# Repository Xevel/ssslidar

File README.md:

# ssslidar
Small Solid State Lidar

The SSSlidar is a (W) 29 x (L) 39 x (H) 21 mm sensor. It is composed of 13 TOF distance sensors, 12 arranged in circular pattern and 1 looking perpendicular to the others.

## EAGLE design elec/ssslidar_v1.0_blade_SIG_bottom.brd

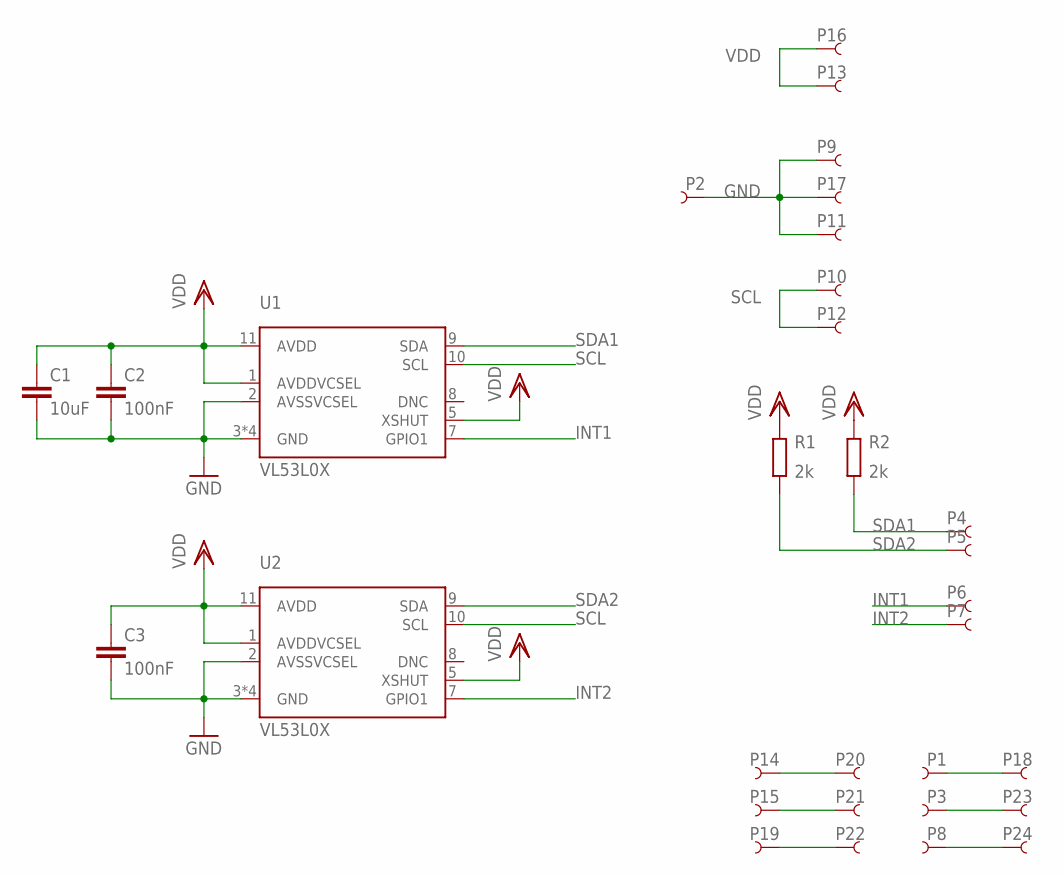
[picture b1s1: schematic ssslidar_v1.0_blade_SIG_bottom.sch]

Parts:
C1: 10uF; 0805_N
C2, C3: 100nF; 0402_N
P1, P3, P4, P5, P6, P7, P8, P14, P15, P18, P19, P20, P21, P22, P23, P24: PIN_SMD_0.8X1_RECT
P2, P9, P10, P11, P12, P13, P16, P17: PIN_SMD_1X2
R1, R2: 2k; 0402_N
U1, U2: VL53L0X

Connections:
GND: C1.2, C2.2, C3.2, P2.P$1, P9.P$1, P11.P$1, P17.P$1, U1.2 (AVSSVCSEL), U1.3 (GND), U1.4 (GND), U1.6 (GND), U1.12 (GND), U2.2 (AVSSVCSEL), U2.3 (GND), U2.4 (GND), U2.6 (GND), U2.12 (GND)
INT1: P6.PIN, U1.7 (GPIO1)
INT2: P7.PIN, U2.7 (GPIO1)
unnamed: P14.PIN, P20.PIN
unnamed: P15.PIN, P21.PIN
unnamed: P19.PIN, P22.PIN
unnamed: P1.PIN, P18.PIN
unnamed: P3.PIN, P23.PIN
unnamed: P8.PIN, P24.PIN
SCL: P10.P$1, P12.P$1, U1.10 (SCL), U2.10 (SCL)
SDA1: P4.PIN, R2.1, U1.9 (SDA)
SDA2: P5.PIN, R1.1, U2.9 (SDA)
VDD: C1.1, C2.1, C3.1, P13.P$1, P16.P$1, R1.2, R2.2, U1.1 (AVDDVCSEL), U1.5 (XSHUT), U1.11 (AVDD), U2.1 (AVDDVCSEL), U2.5 (XSHUT), U2.11 (AVDD)

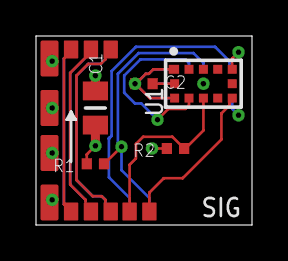
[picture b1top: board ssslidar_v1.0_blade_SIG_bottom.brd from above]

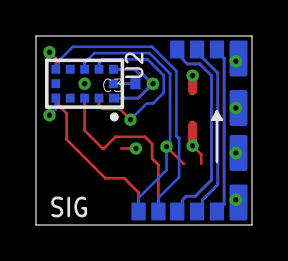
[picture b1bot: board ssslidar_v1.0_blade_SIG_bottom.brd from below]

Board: 4 copper layers, 12.0 x 10.5 mm, 31 parts (14 on the bottom side), 13 nets.

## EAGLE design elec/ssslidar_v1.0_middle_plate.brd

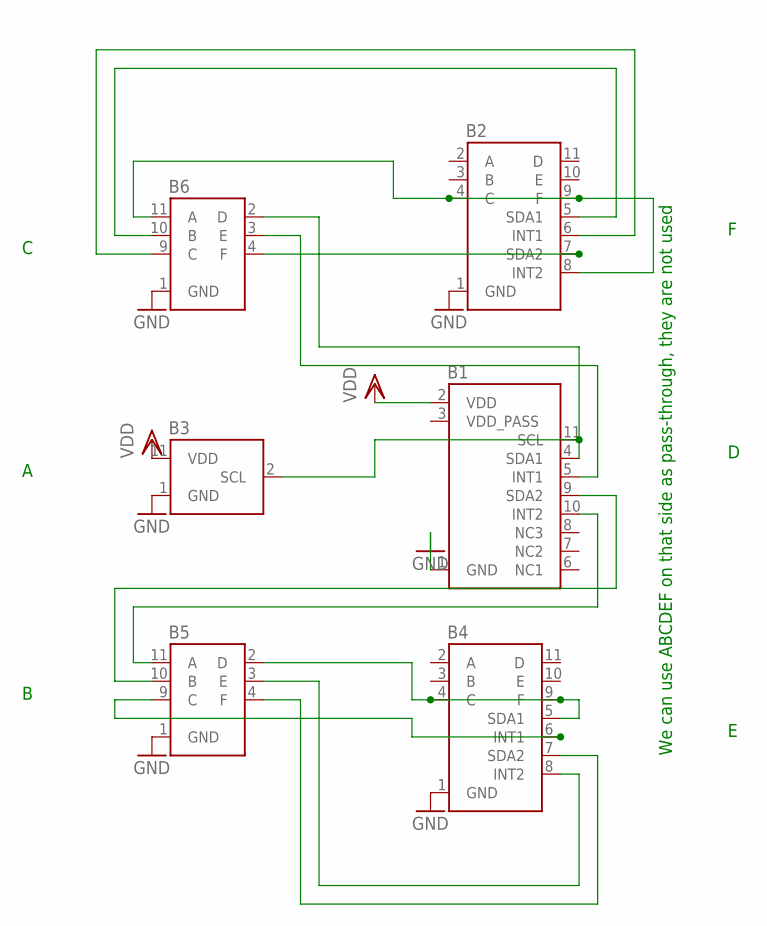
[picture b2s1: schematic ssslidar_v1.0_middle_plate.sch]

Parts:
B1: BLADE_PWR_BOTTOM; BLADE
B2, B4: BLADE_SIG_BOTTOM; BLADE
B3: BLADE_PWR_TOP; BLADE
B5, B6: BLADE_SIG_TOP; BLADE

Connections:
GND: B1.1 (GND), B2.1 (GND), B3.1 (GND), B4.1 (GND), B5.1 (GND), B6.1 (GND)
unnamed: B1.11 (SCL), B3.2 (SCL)
unnamed: B2.4 (C), B2.8 (INT2), B2.9 (F), B6.11 (A)
unnamed: B2.5 (SDA1), B6.10 (B)
unnamed: B2.6 (INT1), B6.9 (C)
unnamed: B1.5 (INT1), B6.3 (E)
unnamed: B2.7 (SDA2), B6.4 (F)
unnamed: B4.8 (INT2), B5.3 (E)
unnamed: B4.4 (C), B4.5 (SDA1), B4.9 (F), B5.2 (D)
unnamed: B4.6 (INT1), B5.9 (C)
unnamed: B1.9 (SDA2), B5.10 (B)
unnamed: B1.10 (INT2), B5.11 (A)
unnamed: B1.4 (SDA1), B6.2 (D)
unnamed: B4.7 (SDA2), B5.4 (F)
VDD: B1.2 (VDD), B3.11 (VDD)

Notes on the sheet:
We can use ABCDEF on that side as pass-through, they are not used

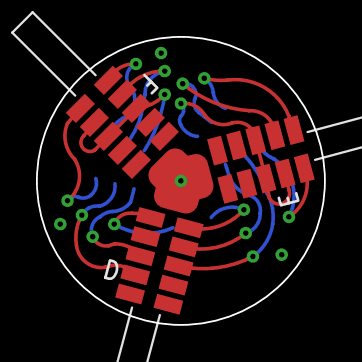
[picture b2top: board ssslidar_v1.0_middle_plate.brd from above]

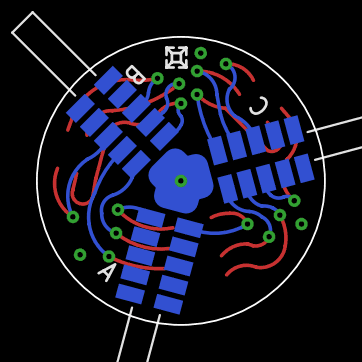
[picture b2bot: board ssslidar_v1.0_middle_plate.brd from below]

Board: 4 copper layers, 16.0 x 16.0 mm, 7 parts (4 on the bottom side), 15 nets.

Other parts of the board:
U$1: XEVELABS_LOGO_S

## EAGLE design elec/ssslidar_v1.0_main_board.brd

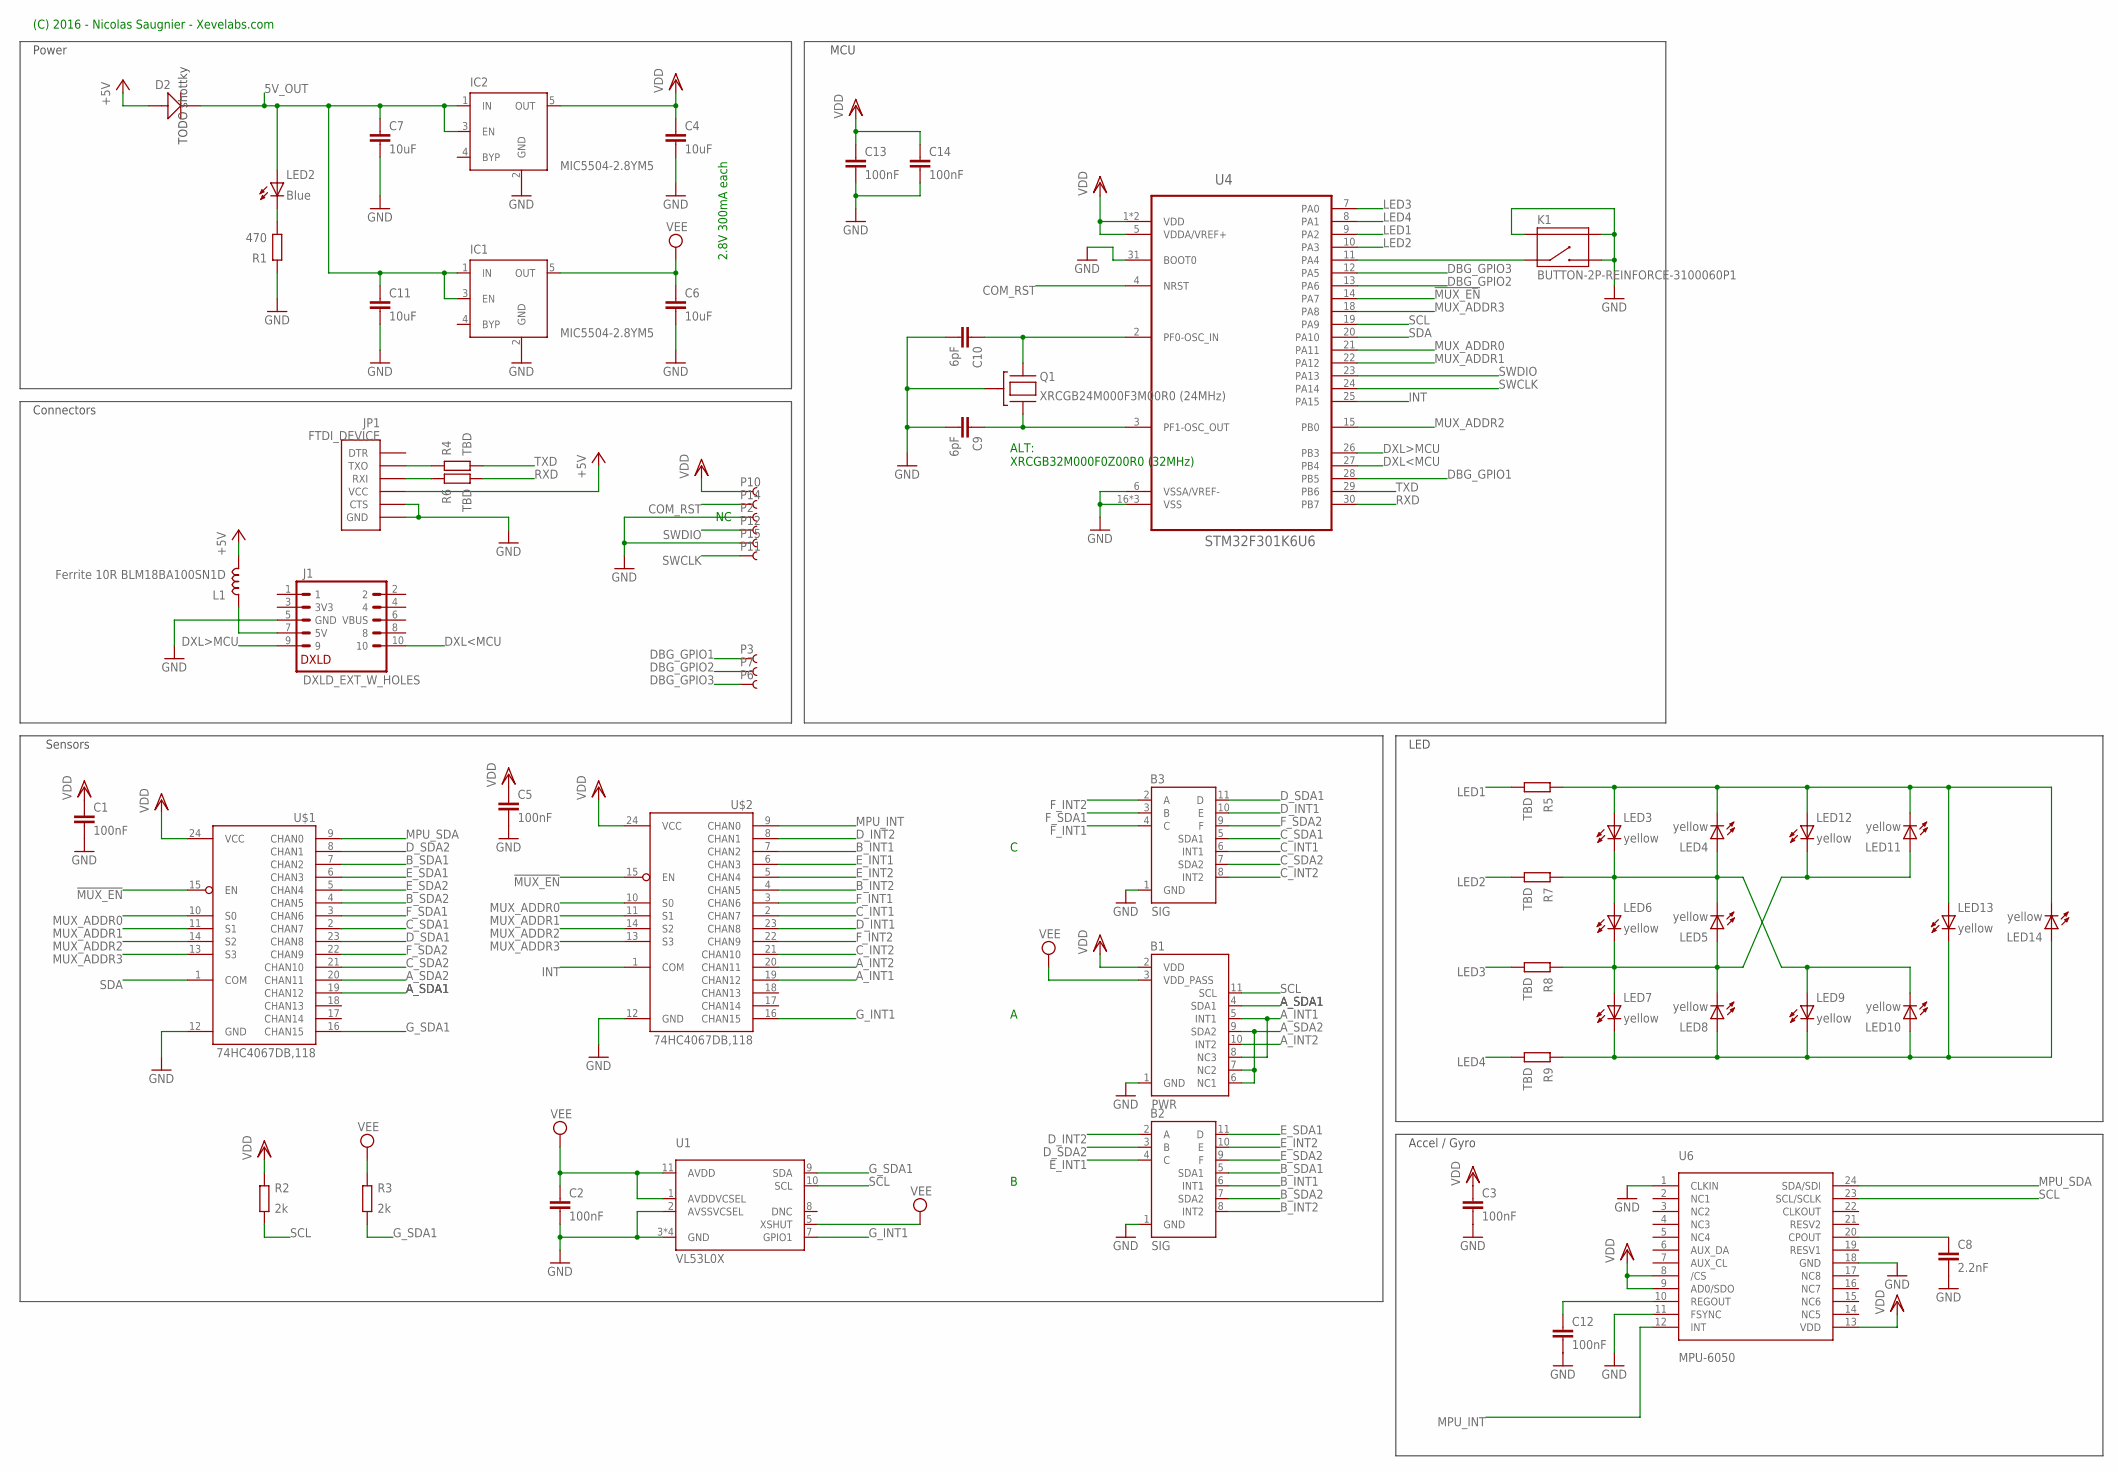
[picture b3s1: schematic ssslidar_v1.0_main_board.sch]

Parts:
B1: PWR; BLADE
B2, B3: SIG; BLADE
C1, C2, C3, C5, C12, C13, C14: 100nF; 0402_N
C4, C6, C7, C11: 10uF; 0805_N
C8: 2.2nF; 0402_N
C9, C10: 6pF; 0402_N
D2: D-SOD-123; SOD123
IC1, IC2: MIC5504-2.8YM5; SOT23-5
J1: DXLD_EXT_W_HOLES
JP1: FTDI_DEVICE; FTDI_DEVICE_SIDE
K1: BUTTON-2P-REINFORCE-3100060P1; 4P-SMD-7.0X3.5X3.5H-90D
L1: Ferrite 10R BLM18BA100SN1D; 0603_N
LED2: Blue; D_0603_N
LED3, LED4, LED5, LED6, LED7, LED8, LED9, LED10, LED11, LED12, LED13, LED14: yellow; D_0603_N
P2, P10, P11, P12, P14, P15: PIN_SMD_1X1.6
P3, P6, P7: PIN_SMD_1X1
Q1: XRCGB24M000F3M00R0 (24MHz); CRYSTAL_2.0X1.6_4P
R1: 470; 0402_N
R2, R3: 2k; 0402_N
R4, R5, R6, R7, R8, R9: TBD; 0402_N
U1: VL53L0X
U4: STM32F301K6U6; QFN50P500X500X60-33N
U6: MPU-6050; QFN-24
U$1, U$2: 74HC4067DB,118; SSOP24

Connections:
5V_OUT: C7.1, C11.1, D2.-, IC1.1 (IN), IC1.3 (EN), IC2.1 (IN), IC2.3 (EN), LED2.A
!MUX_EN: U4.14 (PA7), U$1.15 (EN), U$2.15 (EN)
+5V: D2.+, JP1.P$4 (VCC), L1.2
A_INT1: B1.5 (INT1), B1.8 (NC3), U$2.19 (CHAN12)
A_INT2: B1.10 (INT2), U$2.20 (CHAN11)
A_SDA1: B1.4 (SDA1), U$1.19 (CHAN12)
A_SDA2: B1.6 (NC1), B1.7 (NC2), B1.9 (SDA2), U$1.20 (CHAN11)
B_INT1: B2.6 (INT1), U$2.7 (CHAN2)
B_INT2: B2.8 (INT2), U$2.4 (CHAN5)
B_SDA1: B2.5 (SDA1), U$1.7 (CHAN2)
B_SDA2: B2.7 (SDA2), U$1.4 (CHAN5)
COM_RST: P14.PIN, U4.4 (NRST)
C_INT1: B3.6 (INT1), U$2.2 (CHAN7)
C_INT2: B3.8 (INT2), U$2.21 (CHAN10)
C_SDA1: B3.5 (SDA1), U$1.2 (CHAN7)
C_SDA2: B3.7 (SDA2), U$1.21 (CHAN10)
DBG_GPIO1: P3.P$1, U4.28 (PB5)
DBG_GPIO2: P7.P$1, U4.13 (PA6)
DBG_GPIO3: P6.P$1, U4.12 (PA5)
DXL<MCU: J1.10, U4.27 (PB4)
DXL>MCU: J1.9, U4.26 (PB3)
D_INT1: B3.10 (E), U$2.23 (CHAN8)
D_INT2: B2.2 (A), U$2.8 (CHAN1)
D_SDA1: B3.11 (D), U$1.23 (CHAN8)
D_SDA2: B2.3 (B), U$1.8 (CHAN1)
E_INT1: B2.4 (C), U$2.6 (CHAN3)
E_INT2: B2.10 (E), U$2.5 (CHAN4)
E_SDA1: B2.11 (D), U$1.6 (CHAN3)
E_SDA2: B2.9 (F), U$1.5 (CHAN4)
F_INT1: B3.4 (C), U$2.3 (CHAN6)
F_INT2: B3.2 (A), U$2.22 (CHAN9)
F_SDA1: B3.3 (B), U$1.3 (CHAN6)
F_SDA2: B3.9 (F), U$1.22 (CHAN9)
GND: B1.1 (GND), B2.1 (GND), B3.1 (GND), C1.2, C2.2, C3.2, C4.2, C5.2, C6.2, C7.2, C8.2, C9.2, C10.2, C11.2, C12.2, C13.2, C14.2, IC1.2 (GND), IC2.2 (GND), J1.5 (GND), JP1.P$5 (CTS), JP1.P$6 (GND), K1.2, K1.S1, K1.S2, P2.PIN, P15.PIN, Q1.2 (GND), Q1.4 (GND), R1.2, U1.2 (AVSSVCSEL), U1.3 (GND), U1.4 (GND), U1.6 (GND), U1.12 (GND), U4.6 (VSSA/VREF-), U4.16 (VSS), U4.31 (BOOT0), U4.32 (VSS), U4.33 (VSS), U6.1 (CLKIN), U6.11 (FSYNC), U6.18 (GND), U$1.12 (GND), U$2.12 (GND)
G_INT1: U1.7 (GPIO1), U$2.16 (CHAN15)
G_SDA1: R3.1, U1.9 (SDA), U$1.16 (CHAN15)
INT: U4.25 (PA15), U$2.1 (COM)
LED1: R5.1, U4.9 (PA2)
LED2: R7.1, U4.10 (PA3)
LED3: R8.1, U4.7 (PA0)
LED4: R9.1, U4.8 (PA1)
MPU_INT: U6.12 (INT), U$2.9 (CHAN0)
MPU_SDA: U6.24 (SDA/SDI), U$1.9 (CHAN0)
MUX_ADDR0: U4.21 (PA11), U$1.10 (S0), U$2.10 (S0)
MUX_ADDR1: U4.22 (PA12), U$1.11 (S1), U$2.11 (S1)
MUX_ADDR2: U4.15 (PB0), U$1.14 (S2), U$2.14 (S2)
MUX_ADDR3: U4.18 (PA8), U$1.13 (S3), U$2.13 (S3)
unnamed: C10.1, Q1.1, U4.2 (PF0-OSC_IN)
unnamed: C9.1, Q1.3, U4.3 (PF1-OSC_OUT)
unnamed: K1.1, U4.11 (PA4)
unnamed: J1.7 (5V), L1.1
unnamed: LED2.C, R1.1
unnamed: LED3.A, LED4.C, LED11.C, LED12.A, LED13.A, LED14.C, R5.2
unnamed: LED3.C, LED4.A, LED5.C, LED6.A, LED9.A, LED10.C, R7.2
unnamed: LED5.A, LED6.C, LED7.A, LED8.C, LED11.A, LED12.C, R8.2
unnamed: LED7.C, LED8.A, LED9.C, LED10.A, LED13.C, LED14.A, R9.2
unnamed: JP1.P$2 (TXO), R4.2
unnamed: JP1.P$3 (RXI), R6.2
unnamed: C12.1, U6.10 (REGOUT)
unnamed: C8.1, U6.20 (CPOUT)
RXD: R6.1, U4.30 (PB7)
SCL: B1.11 (SCL), R2.1, U1.10 (SCL), U4.19 (PA9), U6.23 (SCL/SCLK)
SDA: U4.20 (PA10), U$1.1 (COM)
SWCLK: P11.PIN, U4.24 (PA14)
SWDIO: P12.PIN, U4.23 (PA13)
TXD: R4.1, U4.29 (PB6)
VDD: B1.2 (VDD), C1.1, C3.1, C4.1, C5.1, C13.1, C14.1, IC2.5 (OUT), P10.PIN, R2.2, U4.1 (VDD), U4.5 (VDDA/VREF+), U4.17 (VDD), U6.8 (/CS), U6.9 (AD0/SDO), U6.13 (VDD), U$1.24 (VCC), U$2.24 (VCC)
VEE: B1.3 (VDD_PASS), C2.1, C6.1, IC1.5 (OUT), R3.2, U1.1 (AVDDVCSEL), U1.5 (XSHUT), U1.11 (AVDD)

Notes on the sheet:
2.8V 300mA each
Connectors
LED
Power
ALT: XRCGB32M000F0Z00R0 (32MHz)
MCU
(C) 2016 - Nicolas Saugnier - Xevelabs.com
Sensors
TODO shottky
Accel / Gyro

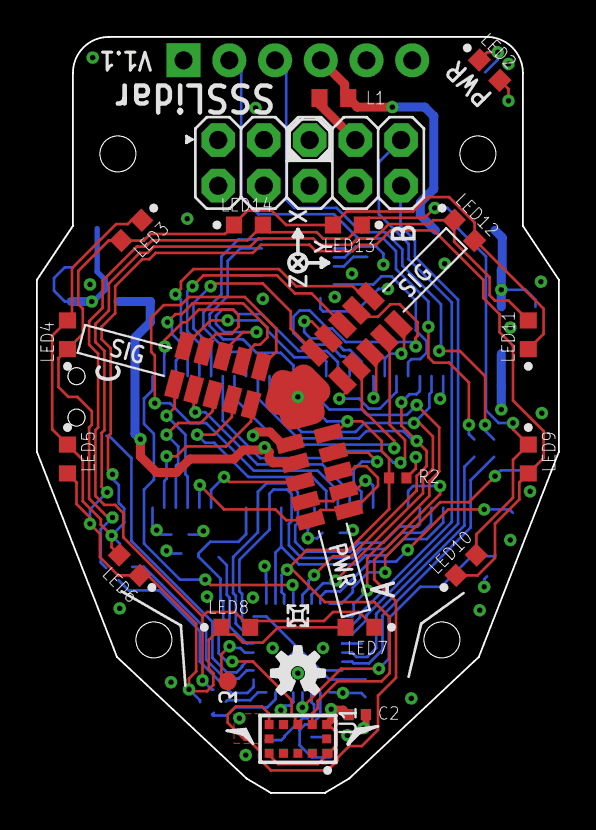
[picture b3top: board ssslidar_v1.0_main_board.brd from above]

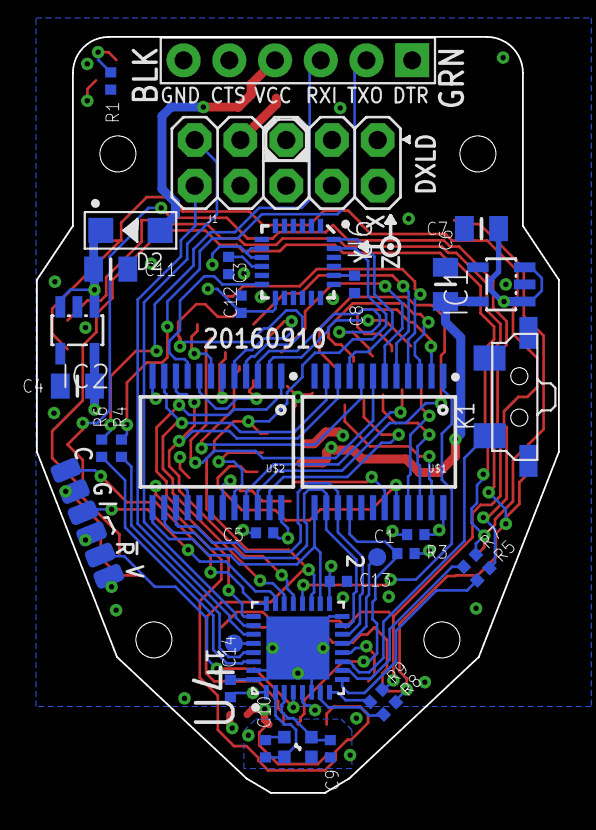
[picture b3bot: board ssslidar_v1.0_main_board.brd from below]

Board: 4 copper layers, 29.0 x 42.0 mm, 63 parts (40 on the bottom side), 68 nets.

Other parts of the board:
U$3: XEVELABS_LOGO_S
U$4: OSHW-LOGO-S

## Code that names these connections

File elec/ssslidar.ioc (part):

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Mcu.Name=STM32F301K(6-8)Ux
Mcu.Package=UFQFPN32
Mcu.UserName=STM32F301K6Ux
PA0.Signal=S_TIM2_CH1_ETR
PA1.Signal=S_TIM2_CH2
PA10.Mode=I2C
PA10.Signal=I2C2_SDA
PA13.Mode=Serial-Wire
PA13.Signal=SYS_JTMS-SWDIO
PA14.Mode=Serial-Wire
PA14.Signal=SYS_JTCK-SWCLK
PA2.Signal=S_TIM2_CH3
PA3.Signal=S_TIM2_CH4
PA9.Mode=I2C
PA9.Signal=I2C2_SCL
PB3.Mode=Asynchronous
PB3.Signal=USART2_TX
PB4.Mode=Asynchronous
PB4.Signal=USART2_RX
PB6.Mode=Asynchronous
PB6.Signal=USART1_TX
PB7.Mode=Asynchronous
PB7.Signal=USART1_RX
PF0-OSC_IN.Mode=HSE-External-Oscillator
PF0-OSC_IN.Signal=RCC_OSC_IN
PF1-OSC_OUT.Mode=HSE-External-Oscillator
PF1-OSC_OUT.Signal=RCC_OSC_OUT
RCC.HSEPLLFreq_Value=8000000
RCC.HSE_VALUE=24000000
RCC.SYSCLKFreq_VALUE=72000000
RCC.SYSCLKSourceVirtual=RCC_SYSCLKSOURCE_PLLCLK

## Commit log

2016-08-12 Added VL53L0X lib Added PWR blade
2016-08-12 Added SIG blade.
2016-08-13 Added middle plate
2016-08-13 Cosmetic improvements on middle plate
2016-08-13 Added main board (wip)
2016-08-14 Working on main board Made blades longer to avoid too much occlusion from the main PCB (but we will still need to put the whole thing on a mast).
2016-09-06 Updated blades (ready for release). Double power rail for sensors.
2016-09-06 Added stm32f301 configuration
2016-09-06 Fixed middle plate with double power rails
2016-09-06 Main board outline and schematics nearly ready
2016-09-06 Added leds, finished sch
2016-09-06 Routing WIP
2016-09-07 Made blades slightly taller (7mm instead of 6.5)
2016-09-07 Routed blades
2016-09-07 LEDs routed. Mostly power left to route.
2016-09-08 Only power and cosmetics left
2016-09-08 Routing done.
2016-09-10 Added MPU-6050 and changed the extension footprint to match the DXLD Interface. Some connections still needed.
2016-09-11 Finalized V1.0.
2016-09-11 Upadted blade footprint, put everything in v1.0
2016-09-11 Separated blades into bottom and top, since the bottom ones need to be taller to avoid seeing the Main PCB, or the screws...
2016-09-11 Blades redesign done.
2016-09-15 Aesthetic modifs
2016-09-15 Updated all libs.

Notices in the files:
parts and their libraries:
SparkFun-AnalogIC: Licensing: CC v3.0 Share-Alike You are welcome to use this library for commercial purposes.
